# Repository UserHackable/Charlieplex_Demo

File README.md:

## Charlieplex Demo Breakout Boards

This set of breakouts can be used to demonstrate how a charlieplex functions. 

The Five Toggle breakout board uses on-off-on single pole, double through toggle switches. This gives each of the five output pins possible values of HIGH, LOW, and INPUT or High Impedance. 

This can then be used to demonstrate how this works with the different layouts of charlieplexed LED's.

## CharlieBreakout 

### Board dimensions

* (130000, 97500) original units
* (1.3000, 0.9750) inches
* (33.0200, 24.7650) mm

[gerbers](CharlieBreakout_gerber.zip?raw=true)

| Front | Back |
| --- | --- |
|  |  |

## CharlieplexedLarsonScannerWandBreakout 

### Board dimensions

* (350000, 40000) original units
* (3.5000, 0.4000) inches
* (88.9000, 10.1600) mm

[gerbers](CharlieplexedLarsonScannerWandBreakout_gerber.zip?raw=true)

| Front | Back |
| --- | --- |
|  |  |

## CharlieplexedPairReactorBreakout 

### Board dimensions

* (110000, 110000) original units
* (1.1000, 1.1000) inches
* (27.9400, 27.9400) mm

[gerbers](CharlieplexedPairReactorBreakout_gerber.zip?raw=true)

| Front | Back |
| --- | --- |
|  |  |

## CharlieReactorBreakout 

### Board dimensions

* (110000, 110000) original units
* (1.1000, 1.1000) inches
* (27.9400, 27.9400) mm

[gerbers](CharlieReactorBreakout_gerber.zip?raw=true)

| Front | Back |
| --- | --- |
|  |  |

## FiveToggleBreakout 

### Board dimensions

* (140001, 99993) original units
* (1.4000, 0.9999) inches
* (35.5603, 25.3982) mm

[gerbers](FiveToggleBreakout_gerber.zip?raw=true)

| Front | Back |
| --- | --- |
|  |  |

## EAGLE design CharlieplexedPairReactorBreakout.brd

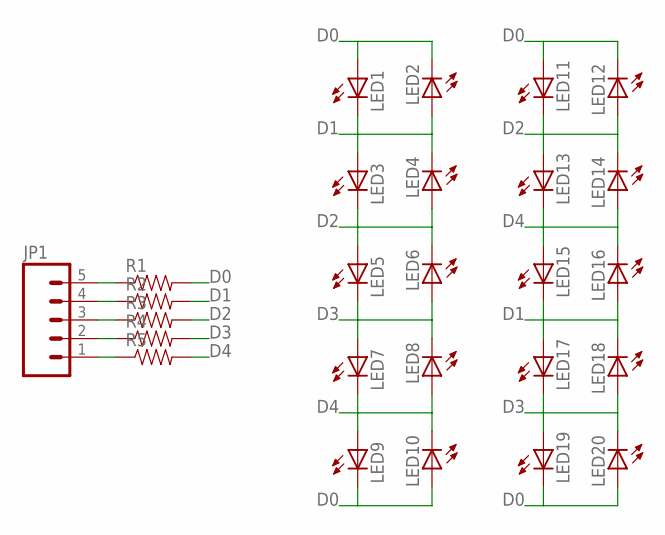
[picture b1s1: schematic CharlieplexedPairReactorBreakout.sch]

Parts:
JP1: M05PTH; 1X05
LED1, LED2, LED3, LED4, LED5, LED6, LED7, LED8, LED9, LED10, LED11, LED12, LED13, LED14, LED15, LED16, LED17, LED18, LED19, LED20: LEDOVAL; LED-OVAL
R1, R2, R3, R4, R5: RESISTORAXIAL-0.3; AXIAL-0.3

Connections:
D0: LED1.ANODE (A), LED2.CATHODE (C), LED9.CATHODE (C), LED10.ANODE (A), LED11.ANODE (A), LED12.CATHODE (C), LED19.CATHODE (C), LED20.ANODE (A), R1.P$2 (2)
D1: LED1.CATHODE (C), LED2.ANODE (A), LED3.ANODE (A), LED4.CATHODE (C), LED15.CATHODE (C), LED16.ANODE (A), LED17.ANODE (A), LED18.CATHODE (C), R2.P$2 (2)
D2: LED3.CATHODE (C), LED4.ANODE (A), LED5.ANODE (A), LED6.CATHODE (C), LED11.CATHODE (C), LED12.ANODE (A), LED13.ANODE (A), LED14.CATHODE (C), R3.P$2 (2)
D3: LED5.CATHODE (C), LED6.ANODE (A), LED7.ANODE (A), LED8.CATHODE (C), LED17.CATHODE (C), LED18.ANODE (A), LED19.ANODE (A), LED20.CATHODE (C), R4.P$2 (2)
D4: LED7.CATHODE (C), LED8.ANODE (A), LED9.ANODE (A), LED10.CATHODE (C), LED13.CATHODE (C), LED14.ANODE (A), LED15.ANODE (A), LED16.CATHODE (C), R5.P$2 (2)
MISO: JP1.4, R2.P$1 (1)
MOSI: JP1.5, R1.P$1 (1)
PB3: JP1.2, R4.P$1 (1)
PB4: JP1.1, R5.P$1 (1)
SCK: JP1.3, R3.P$1 (1)

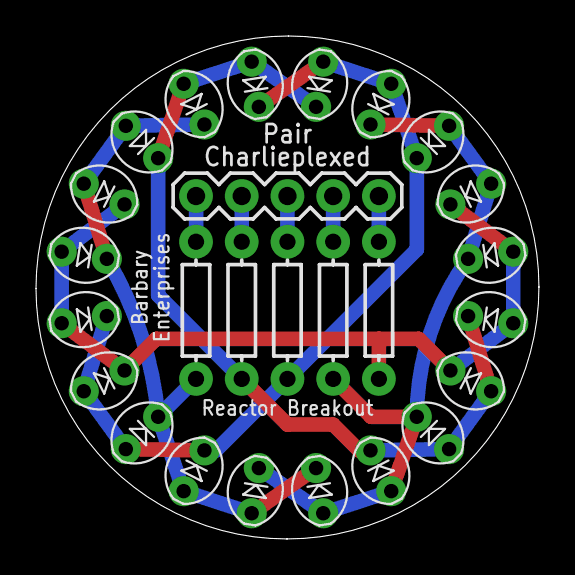
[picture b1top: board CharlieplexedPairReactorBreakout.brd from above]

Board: 2 copper layers, 27.9 x 27.9 mm, 26 parts (0 on the bottom side), 10 nets.

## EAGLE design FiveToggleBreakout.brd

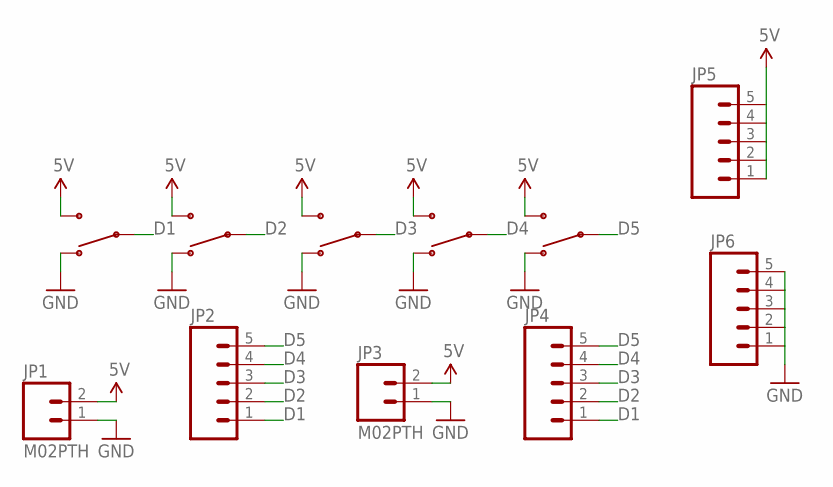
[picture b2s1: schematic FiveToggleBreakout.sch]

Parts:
JP1, JP3: M02PTH; 1X02
JP2, JP4, JP5, JP6: M05PTH; 1X05
U$1, U$2, U$3, U$4, U$5: SPDTSPDT; TOGGLE_SPDT

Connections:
5V: JP1.2, JP3.2, JP5.1, JP5.2, JP5.3, JP5.4, JP5.5, U$1.3, U$2.3, U$3.3, U$4.3, U$5.3
D1: JP2.1, JP4.1, U$1.2
D2: JP2.2, JP4.2, U$2.2
D3: JP2.3, JP4.3, U$3.2
D4: JP2.4, JP4.4, U$4.2
D5: JP2.5, JP4.5, U$5.2
GND: JP1.1, JP3.1, JP6.1, JP6.2, JP6.3, JP6.4, JP6.5, U$1.1, U$2.1, U$3.1, U$4.1, U$5.1

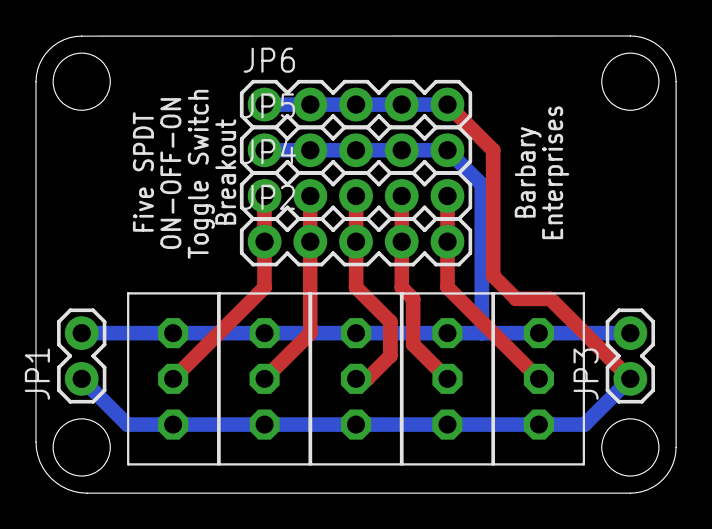
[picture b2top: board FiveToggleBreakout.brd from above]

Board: 2 copper layers, 35.6 x 25.4 mm, 11 parts (0 on the bottom side), 7 nets.

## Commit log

2016-04-08 from Makefile

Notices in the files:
parts and their libraries:
SparkFun-Connectors: Licensing: Creative Commons ShareAlike 4.0 International - https://creativecommons.org/licenses/by-sa/4.0
